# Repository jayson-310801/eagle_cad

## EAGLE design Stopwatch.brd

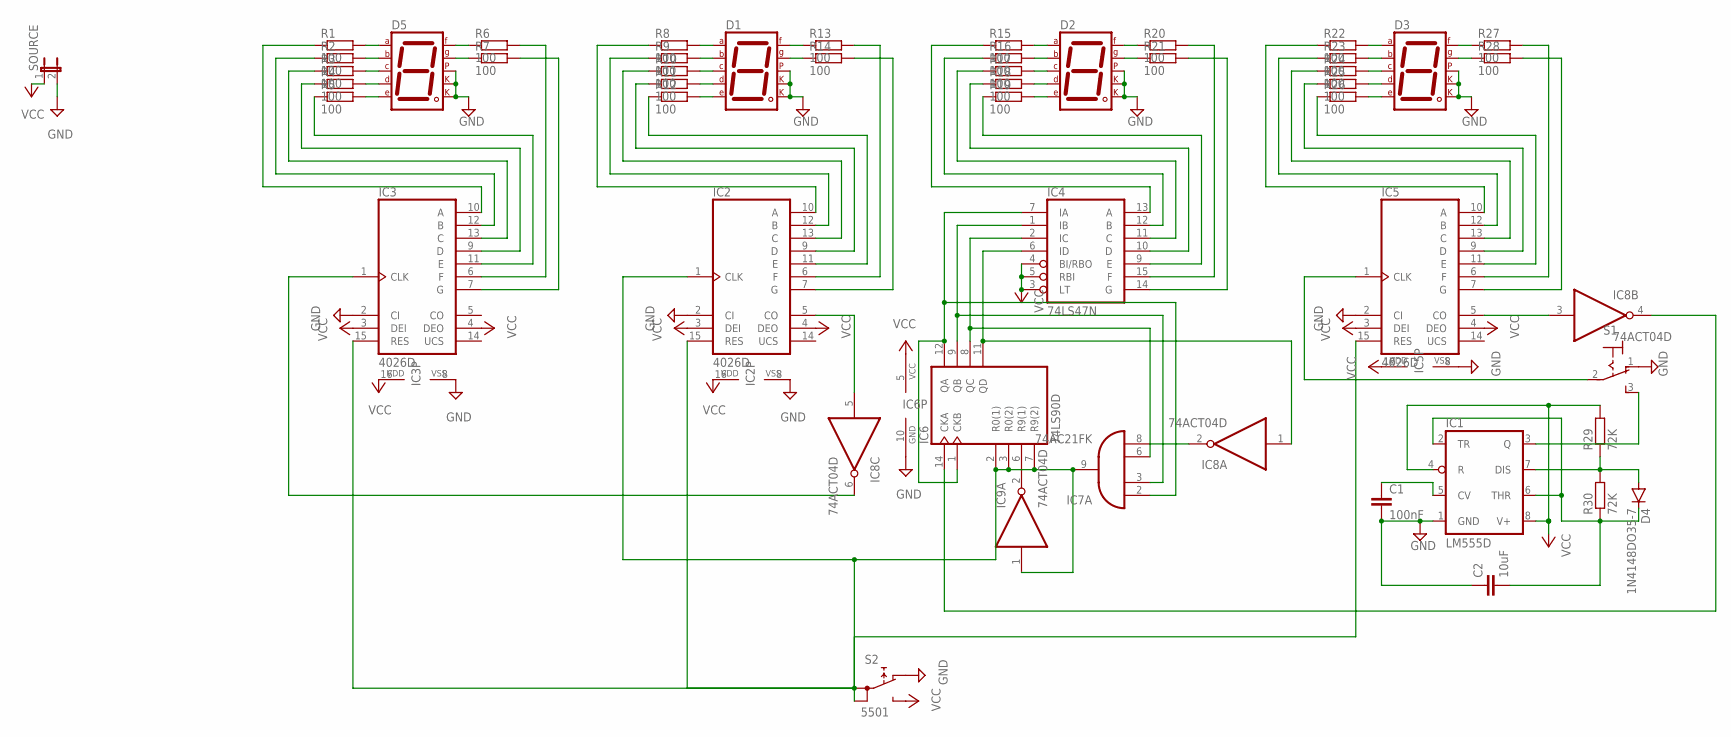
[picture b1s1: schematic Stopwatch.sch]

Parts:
C1: 100nF; C2.5-2
C2: 10uF; C2.5-2
D1, D2, D3, D5: 7SEG-CK; 7SEG-13
D4: 1N4148DO35-7; DO35-7
IC1: LM555D; SO08
IC2, IC3, IC5: 4026D; SO16
IC4: 74LS47N; DIL16
IC6: 74LS90D; SO14
IC7: 74AC21FK; LCC20
IC8, IC9: 74ACT04D; SO14
R1, R2, R3, R4, R5, R6, R7, R8, R9, R10, R11, R12, R13, R14, R15, R16, R17, R18, R19, R20, R21, R22, R23, R24, R25, R26, R27, R28: 100; R0805
R29, R30: 72K; R0805
S1: 320-916
S2: 5501
SOURCE: JP1E; JP1

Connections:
GND: C1.2, C2.1, D1.3 (CK1), D1.5 (DP), D1.8 (CK2), D2.3 (CK1), D2.5 (DP), D2.8 (CK2), D3.3 (CK1), D3.5 (DP), D3.8 (CK2), D5.3 (CK1), D5.5 (DP), D5.8 (CK2), IC1.1 (GND), IC2.2 (CI), IC2.8 (VSS), IC3.2 (CI), IC3.8 (VSS), IC4.8 (GND), IC5.2 (CI), IC5.8 (VSS), IC6.10 (GND), IC7.10 (GND), IC8.7 (GND), IC9.7 (GND), S1.1 (O), S2.NC, SOURCE.2
unnamed: IC2.10 (A), R8.1
unnamed: IC2.12 (B), R9.1
unnamed: IC3.10 (A), R1.1
unnamed: IC3.12 (B), R2.1
unnamed: IC3.13 (C), R3.1
unnamed: IC3.9 (D), R4.1
unnamed: IC3.11 (E), R5.1
unnamed: IC3.6 (F), R6.2
unnamed: IC3.7 (G), R7.2
unnamed: D5.7 (A), R1.2
unnamed: D5.6 (B), R2.2
unnamed: D5.4 (C), R3.2
unnamed: D5.2 (D), R4.2
unnamed: D5.1 (E), R5.2
unnamed: D5.9 (F), R6.1
unnamed: D5.10 (G), R7.1
unnamed: IC2.13 (C), R10.1
unnamed: IC2.9 (D), R11.1
unnamed: IC2.11 (E), R12.1
unnamed: IC2.6 (F), R13.2
unnamed: IC2.7 (G), R14.2
unnamed: D1.7 (A), R8.2
unnamed: D1.6 (B), R9.2
unnamed: D1.4 (C), R10.2
unnamed: D1.2 (D), R11.2
unnamed: D1.1 (E), R12.2
unnamed: D1.9 (F), R13.1
unnamed: D1.10 (G), R14.1
unnamed: IC4.13 (A), R15.1
unnamed: IC4.12 (B), R16.1
unnamed: IC4.11 (C), R17.1
unnamed: IC4.10 (D), R18.1
unnamed: IC4.9 (E), R19.1
unnamed: IC4.15 (F), R20.2
unnamed: IC4.14 (G), R21.2
unnamed: D2.7 (A), R15.2
unnamed: D2.6 (B), R16.2
unnamed: D2.4 (C), R17.2
unnamed: D2.2 (D), R18.2
unnamed: D2.1 (E), R19.2
unnamed: D2.9 (F), R20.1
unnamed: D2.10 (G), R21.1
unnamed: IC5.10 (A), R22.1
unnamed: IC5.12 (B), R23.1
unnamed: IC5.13 (C), R24.1
unnamed: IC5.9 (D), R25.1
unnamed: IC5.11 (E), R26.1
unnamed: IC5.6 (F), R27.2
unnamed: IC5.7 (G), R28.2
unnamed: D3.7 (A), R22.2
unnamed: D3.6 (B), R23.2
unnamed: D3.4 (C), R24.2
unnamed: D3.2 (D), R25.2
unnamed: D3.1 (E), R26.2
unnamed: D3.9 (F), R27.1
unnamed: D3.10 (G), R28.1
unnamed: C1.1, IC1.5 (CV)
unnamed: IC5.1 (CLK), S1.2
unnamed: C2.2, D4.C, IC1.2 (TR), IC1.6 (THR), R30.1
unnamed: D4.A, IC1.7 (DIS), R29.1, R30.2
unnamed: IC4.7 (IA), IC6.1 (CKB), IC6.12 (QA), IC7.2 (I0)
unnamed: IC4.1 (IB), IC6.9 (QB), IC7.3 (I1)
unnamed: IC4.2 (IC), IC6.8 (QC), IC7.6 (I2)
unnamed: IC4.6 (ID), IC6.11 (QD), IC8.1 (I)
unnamed: IC7.8 (I3), IC8.2 (O)
unnamed: IC5.5 (CO), IC8.3 (I)
unnamed: IC6.14 (CKA), IC8.4 (O)
unnamed: IC2.5 (CO), IC8.5 (I)
unnamed: IC3.1 (CLK), IC8.6 (O)
unnamed: IC1.3 (Q), S1.3 (S)
unnamed: IC6.6 (R9(1)), IC9.2 (O)
unnamed: IC2.1 (CLK), IC2.15 (RES), IC3.15 (RES), IC5.15 (RES), IC6.2 (R0(1)), IC6.3 (R0(2)), IC6.7 (R9(2)), IC7.9 (O), IC9.1 (I), S2.1A, S2.1B
VCC: IC1.4 (R), IC1.8 (V+), IC2.3 (DEI), IC2.4 (DEO), IC2.16 (VDD), IC3.3 (DEI), IC3.4 (DEO), IC3.16 (VDD), IC4.3 (LT), IC4.4 (BI/RBO), IC4.5 (RBI), IC4.16 (VCC), IC5.3 (DEI), IC5.4 (DEO), IC5.16 (VDD), IC6.5 (VCC), IC7.20 (VCC), IC8.14 (VCC), IC9.14 (VCC), R29.2, S2.NO, SOURCE.1

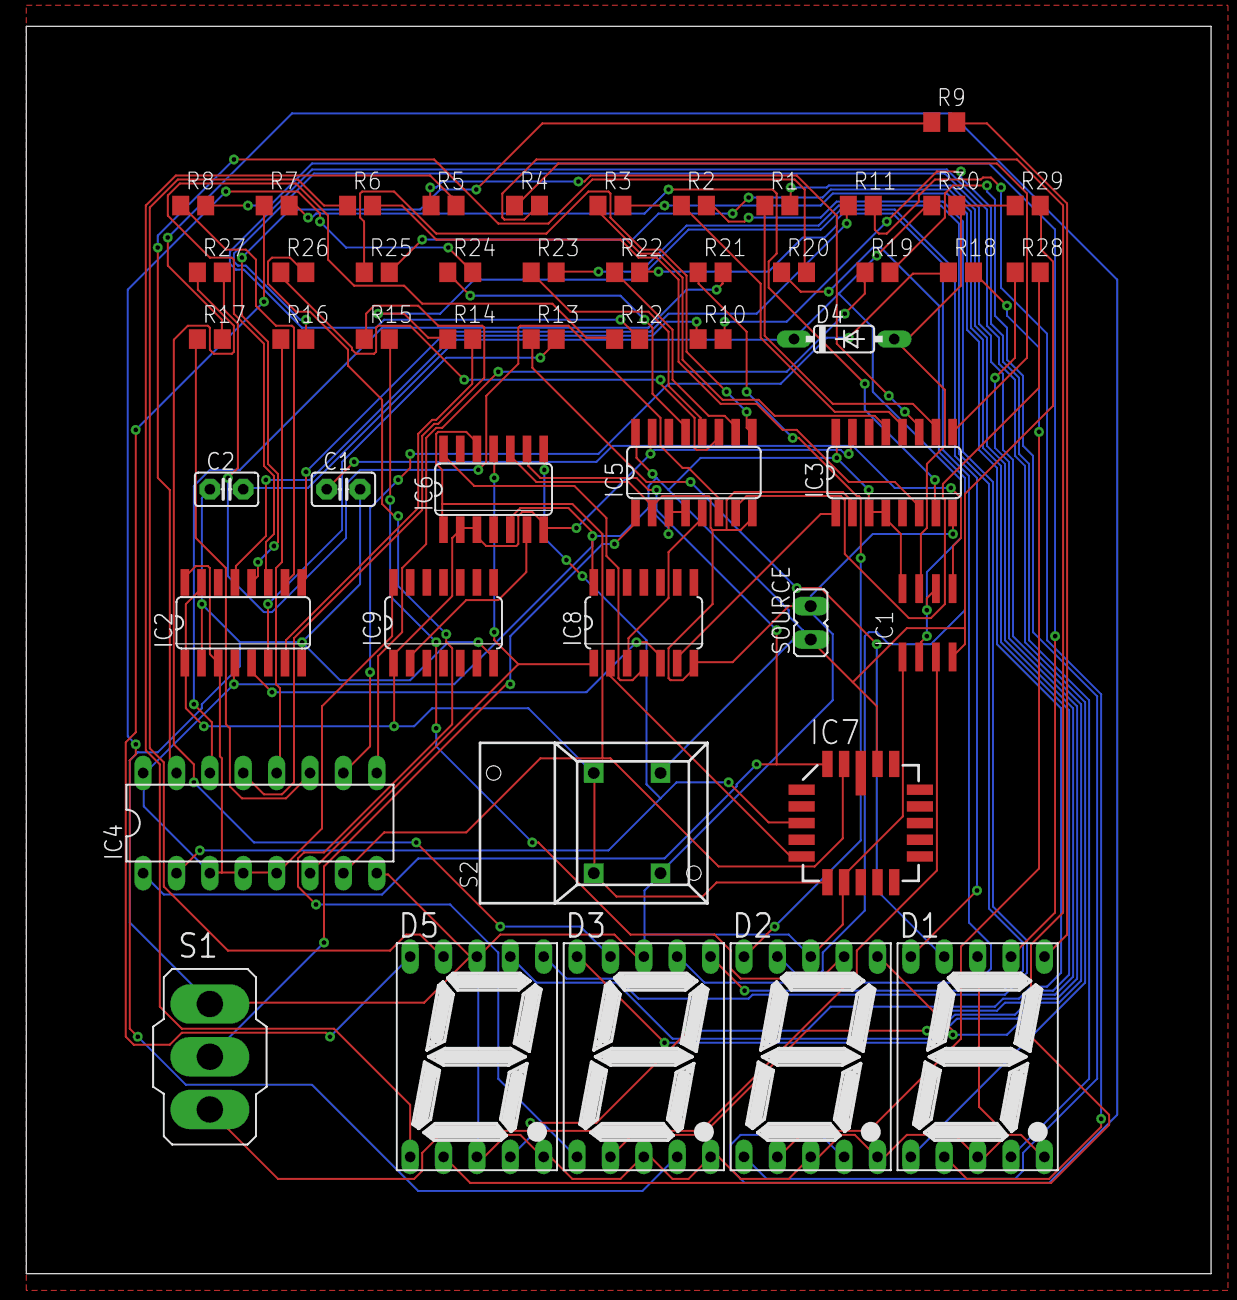
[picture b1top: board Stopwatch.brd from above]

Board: 2 copper layers, 90.1 x 94.9 mm, 49 parts (0 on the bottom side), 74 nets.
